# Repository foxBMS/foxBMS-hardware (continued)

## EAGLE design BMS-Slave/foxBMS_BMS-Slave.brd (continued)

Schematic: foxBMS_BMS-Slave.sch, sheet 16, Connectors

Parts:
X1601, X1602: 43045-0406_MOLEX_4PIN; X_SMD_MOLEX_43045-0408_R_REV01
X1603: 43045-1606_MOLEX_16PIN; X_SMD_MOLEX_43045-1608_R_REV01
X1604, X1607, X1608: MA10-2
X1605: MA09-2
X1606: 43045-2406_MOLEX_24PIN; X_SMD_MOLEX_43045-2408_R_REV01

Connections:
+3.0V_VREF2_0: X1604.18; also elsewhere on the board
+3.0V_VREF2_1: X1604.17; also elsewhere on the board
+5.0V_VREG_0: X1604.16; also elsewhere on the board
+5.0V_VREG_1: X1604.15; also elsewhere on the board
CELL_0+: X1603.2; also elsewhere on the board
CELL_0-: X1603.9; also elsewhere on the board
CELL_1+: X1603.10; also elsewhere on the board
CELL_2+: X1603.3; also elsewhere on the board
CELL_3+: X1603.11; also elsewhere on the board
CELL_4+: X1603.4; also elsewhere on the board
CELL_5+: X1603.12; also elsewhere on the board
CELL_6+: X1603.5; also elsewhere on the board
CELL_7+: X1603.13; also elsewhere on the board
CELL_8+: X1603.6; also elsewhere on the board
CELL_9+: X1603.14; also elsewhere on the board
CELL_10+: X1603.7; also elsewhere on the board
CELL_11+: X1603.15; also elsewhere on the board
FUSED_VBAT-: X1605.17, X1605.18, X1606.1, X1606.2, X1606.3, X1606.4, X1606.5, X1606.6, X1606.7, X1606.8, X1606.9, X1606.10, X1606.11, X1606.12, X1607.2, X1607.4, X1607.6, X1607.8, X1607.10, X1607.12, X1607.14, X1607.16, X1607.18, X1607.20, X1608.2, X1608.4, X1608.6, X1608.8, X1608.10, X1608.12, X1608.14, X1608.16, X1608.18, X1608.20; also elsewhere on the board
PRIMARY-GPIO0-OPT: X1604.6; also elsewhere on the board
PRIMARY-GPIO1: X1604.8; also elsewhere on the board
PRIMARY-GPIO2: X1604.10; also elsewhere on the board
PRIMARY-GPIO3-OPT: X1604.12; also elsewhere on the board
PRIMARY-GPIO4-OPT: X1604.14; also elsewhere on the board
PRIMARY-IN+_P: X1601.1; also elsewhere on the board
PRIMARY-IN-_N: X1601.3; also elsewhere on the board
PRIMARY-OUT+_P: X1601.4; also elsewhere on the board
PRIMARY-OUT-_N: X1601.2; also elsewhere on the board
PRIMARY-WDT: X1604.20; also elsewhere on the board
PRIMARY_D/A_INPUT_0: X1605.1; also elsewhere on the board
PRIMARY_D/A_INPUT_1: X1605.2; also elsewhere on the board
PRIMARY_D/A_INPUT_2: X1605.3; also elsewhere on the board
PRIMARY_D/A_INPUT_3: X1605.4; also elsewhere on the board
PRIMARY_D/A_INPUT_4: X1605.5; also elsewhere on the board
PRIMARY_D/A_INPUT_5: X1605.6; also elsewhere on the board
PRIMARY_D/A_INPUT_6: X1605.7; also elsewhere on the board
PRIMARY_D/A_INPUT_7: X1605.8; also elsewhere on the board
PRIMARY_D/A_INPUT_8: X1605.9; also elsewhere on the board
PRIMARY_D/A_INPUT_9: X1605.10; also elsewhere on the board
PRIMARY_D/A_INPUT_10: X1605.11; also elsewhere on the board
PRIMARY_D/A_INPUT_11: X1605.12; also elsewhere on the board
PRIMARY_D/A_INPUT_12: X1605.13; also elsewhere on the board
PRIMARY_D/A_INPUT_13: X1605.14; also elsewhere on the board
PRIMARY_D/A_INPUT_14: X1605.15; also elsewhere on the board
PRIMARY_D/A_INPUT_15: X1605.16; also elsewhere on the board
SECONDARY-GPIO0-OPT: X1604.5; also elsewhere on the board
SECONDARY-GPIO1: X1604.7; also elsewhere on the board
SECONDARY-GPIO2: X1604.9; also elsewhere on the board
SECONDARY-GPIO3-OPT: X1604.11; also elsewhere on the board
SECONDARY-GPIO4-OPT: X1604.13; also elsewhere on the board
SECONDARY-IN+_P: X1602.1; also elsewhere on the board
SECONDARY-IN-_N: X1602.3; also elsewhere on the board
SECONDARY-OUT+_P: X1602.4; also elsewhere on the board
SECONDARY-OUT-_N: X1602.2; also elsewhere on the board
SECONDARY-WDT: X1604.19; also elsewhere on the board
SECONDARY_D/A_INPUT_0: X1604.1; also elsewhere on the board
SECONDARY_D/A_INPUT_1: X1604.2; also elsewhere on the board
SECONDARY_D/A_INPUT_2: X1604.3; also elsewhere on the board
SECONDARY_D/A_INPUT_3: X1604.4; also elsewhere on the board
T-SENSOR_0: X1606.24; also elsewhere on the board
T-SENSOR_1: X1606.23; also elsewhere on the board
T-SENSOR_2: X1606.22; also elsewhere on the board
T-SENSOR_3: X1606.21; also elsewhere on the board
T-SENSOR_4: X1606.20; also elsewhere on the board
T-SENSOR_5: X1606.19; also elsewhere on the board
T-SENSOR_6: X1607.1; also elsewhere on the board
T-SENSOR_7: X1607.3; also elsewhere on the board
T-SENSOR_8: X1607.5; also elsewhere on the board
T-SENSOR_9: X1607.7; also elsewhere on the board
T-SENSOR_10: X1607.9; also elsewhere on the board
T-SENSOR_11: X1607.11; also elsewhere on the board
T-SENSOR_12: X1607.13; also elsewhere on the board
T-SENSOR_13: X1607.15; also elsewhere on the board
T-SENSOR_14: X1607.17; also elsewhere on the board
T-SENSOR_15: X1607.19; also elsewhere on the board
T-SENSOR_16: X1606.18; also elsewhere on the board
T-SENSOR_17: X1606.17; also elsewhere on the board
T-SENSOR_18: X1606.16; also elsewhere on the board
T-SENSOR_19: X1606.15; also elsewhere on the board
T-SENSOR_20: X1606.14; also elsewhere on the board
T-SENSOR_21: X1606.13; also elsewhere on the board
T-SENSOR_22: X1608.19; also elsewhere on the board
T-SENSOR_23: X1608.17; also elsewhere on the board
T-SENSOR_24: X1608.15; also elsewhere on the board
T-SENSOR_25: X1608.13; also elsewhere on the board
T-SENSOR_26: X1608.11; also elsewhere on the board
T-SENSOR_27: X1608.9; also elsewhere on the board
T-SENSOR_28: X1608.7; also elsewhere on the board
T-SENSOR_29: X1608.5; also elsewhere on the board
T-SENSOR_30: X1608.3; also elsewhere on the board
T-SENSOR_31: X1608.1; also elsewhere on the board
VBAT+: X1603.16; also elsewhere on the board
VBAT-: X1603.1; also elsewhere on the board

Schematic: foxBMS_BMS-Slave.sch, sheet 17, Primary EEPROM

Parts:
C1701: 100nF, 20%, 16V; 0603
IC1701: 24AA02UID; IC_SMD_SOT23-5_R_MICROCHIP_REV01

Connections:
+5.0V_VREG_0: C1701.2, IC1701.4 (VCC); also elsewhere on the board
FUSED_VBAT-: C1701.1, IC1701.2 (VSS); also elsewhere on the board
PRIMARY-SCL: IC1701.1 (SCL); also elsewhere on the board
PRIMARY-SDA: IC1701.3 (SDA); also elsewhere on the board

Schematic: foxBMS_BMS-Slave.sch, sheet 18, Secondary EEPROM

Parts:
C1801: 100nF, 20%, 16V; 0603
IC1801: 24AA02UID; IC_SMD_SOT23-5_R_MICROCHIP_REV01

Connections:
+5.0V_VREG_1: C1801.2, IC1801.4 (VCC); also elsewhere on the board
FUSED_VBAT-: C1801.1, IC1801.2 (VSS); also elsewhere on the board
SECONDARY-SCL: IC1801.1 (SCL); also elsewhere on the board
SECONDARY-SDA: IC1801.3 (SDA); also elsewhere on the board

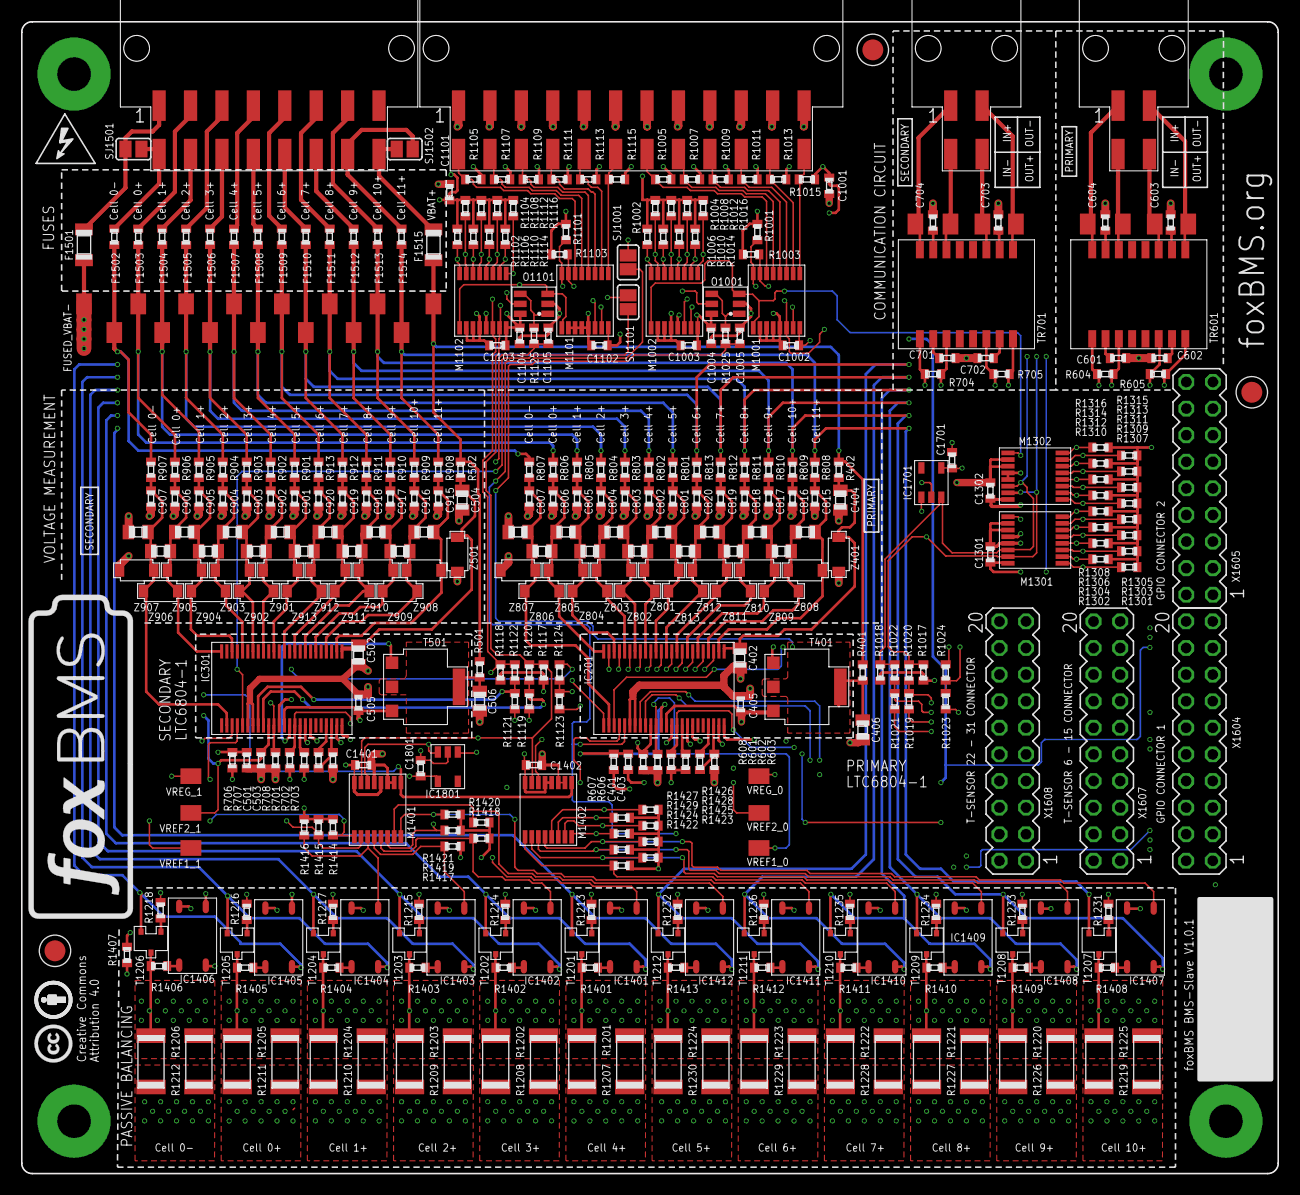
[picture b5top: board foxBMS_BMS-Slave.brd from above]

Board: 6 copper layers, 120.0 x 110.0 mm, 394 parts (0 on the bottom side), 244 nets.

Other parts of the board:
U$50, U$52, U$62: FIDUCIAL_1MM

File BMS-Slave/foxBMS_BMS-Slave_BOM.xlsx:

Populate | Qty | Value | Device | Package | Parts | Comments | Farnell | Digikey | Mouser
Resistor
yes | 10 | 0R | R_0603 | 603 | R601 R607 R701 R707 R1020 R1022 R1024 R1120 R1122 R1124 | Resistor | 2059527
yes | 2 | 1.21k, 1%, 1/10W | R_0603 | 603 | R603 R703 | Resistor | 2059331
yes | 32 | 100R, 1%, 1/10W | R_0603 | 603 | R401 R402 R501 R502 R801 R802 R803 R804 R805 R806 R807 R808 R809 R810 R811 R812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 | Resistor | 2059574
yes | 32 | 10k, 10%, 1/10W | R_0603 | 603 | R1301 R1302 R1303 R1304 R1305 R1306 R1307 R1308 R1309 R1310 R1311 R1312 R1313 R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 | Resistor | 2303192
yes | 24 | 75R, 10%, 0.4W | R2010 | 2010 | R1201 R1202 R1203 R1204 R1205 R1206 R1207 R1208 R1209 R1210 R1211 R1212 R1219 R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 | Resistor | 2059282
yes | 4 | 120R, 1%, 1/10W | R_0603 | 603 | R604 R605 R704 R705 | Resistor | 2303067
yes | 2 | 1M, 10%, 1/10W | R_0603 | 603 | R608 R708 | Resistor | 2059679
yes | 1 | 1k, 10%, 1/10W | R_0603 | 603 | R1407 | Resistor | 2059601
yes | 12 | 130R, 10%, 1/10W | R_0603 | 603 | R1401 R1402 R1403 R1404 R1405 R1406 R1408 R1409 R1410 R1411 R1412 R1413 | Resistor | 2059288
yes | 32 | 20k, 1%, 1/10W | R_0603 | 603 | R1001 R1002 R1003 R1004 R1005 R1006 R1007 R1008 R1009 R1010 R1011 R1012 R1013 R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 | Resistor | 2059636
yes | 12 | 3.3k, 10%, 1/10W | R_0603 | 603 | R1213 R1214 R1215 R1216 R1217 R1218 R1231 R1232 R1233 R1234 R1235 R1236 | Resistor | 2059614
yes | 4 | 4.7k, 10%, 1/10W | R_0603 | 603 | R1017 R1018 R1117 R1118 | Resistor | 2059619
yes | 2 | 806, 1%, 1/10W | R_0603 | 603 | R602 R702 | Resistor | 2059324 | 541-806HCT-ND
Capacitor
yes | 6 | 100nF, 10%, 100V | C_0805 | 805 | C402 C404 C406 C502 C504 C506 | Capacitor | 1856515
yes | 4 | 100nF, 20%, 16V | C_0603 | 603 | C1001 C1101 C1701 C1801 | Capacitor | 1828890
yes | 4 | 100pF, 15%, 25V | C_0603 | 603 | C601 C602 C701 C702 | Capacitor | 1856386
yes | 28 | 10nF, 100V, 10% | C_0603 | 603 | C801 C802 C803 C804 C805 C806 C807 C815 C816 C817 C818 C819 C820 C901 C902 C903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 | Capacitor | 1865545
yes | 16 | 1uF, 20%, 16V | C_0603 | 603 | C401 C403 C405 C501 C503 C505 C1002 C1003 C1004 C1102 C1103 C1104 C1301 C1302 C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 | Capacitor | 1907343
yes | 4 | 1uF, 20%, 25V | C_0603 | 603 | C603 C604 C703 C704 | Capacitor | 2470425
Diode
yes | 26 | 6.8V, 500mW | MMSZ5235BT1G | SOD123 | Z801 Z802 Z803 Z804 Z805 Z806 Z807 Z808 Z809 Z810 Z811 Z812 Z813 Z901 Z902 Z903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 | ON SEMICONDUCTOR | 1431277
yes | 2 | 60V,500mW | MMSZ5264B-V-GS08 | SOD123 | Z401 Z501 | MMSZ_xVx_T1 Seri | 1895056
yes | 12 | CPC1008N | CPC1008N | SOP4 | IC1401 IC1402 IC1403 IC1404 IC1405 IC1406 IC1407 IC1408 IC1409 IC1410 IC1411 IC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 | CLARE - Single-Po | 1653755
IC
yes | 8 | LTC1380-GN | LTC1380-GN | SSOP16 | M1001 M1002 M1101 M1102 M1301 M1302 M1401 M1402 |  | 2295514
yes | 2 | LTC6255CS6PBF | LTC6255CS6PBF | SOT95P280X100-6N | O1001 O1101 | Op Amps |  | LTC6255CS6#TRMPBFCT-ND
yes | 2 | LTC6804-1 | LTC6804-1 | SSOP48 | IC201 IC301 |  |  | LTC6804HG-1#PBF-ND
yes | 2 | 24AA02UID | SOT-23 | SOT-23 | IC1701 IC1801 | EEPROM IC | 2345557 | 24AA02UIDT-I/OTCT-ND | 579-24AA02UIDT-I/OT
Connector
yes | 1 | MA09-2 | MA09-2 | MA09-2 | X1605 | PIN HEADER | 2025256
yes | 3 | MA10-2 | MA10-2 | MA10-2 | X1604 X1607 X1608 | PIN HEADER | 2025257
yes | 1 |  | HEADER_POS16_43045-1606 | 43045-1606 | X1603 | Molex - Micro-Fit |  | WM10739CT-ND
yes | 1 |  | HEADER_POS24_43045-2406 | 43045-2406 | X1606 | Molex - Micro-Fit |  | WM10768CT-ND
yes | 2 |  | HEADER_POS4_43045-0406 | 43045-0406 | X1601 X1602 | Molex - Micro-Fit | 2063766 | WM3249CT-ND
Transistor
yes | 12 | NX2301P | NX2301P | SOT23 | T1201 T1202 T1203 T1204 T1205 T1206 T1207 T1208 T1209 T1210 T1211 T1212 | #2245 | 1894738
yes | 2 | PBHV8115Z | NPN-223 | SOT-223 | T401 T501 |  | 1829309
Misc
yes | 2 | 0.5A, 63V, 0.25R | R_MET_1206 | 1206 | F1501 F1515 | Resistor |  | F1454CT-ND
yes | 2 | HX1188NL | HX1188NL | HX1188NL | T601 T701 |  |  | 553-1536-1-ND
yes | 13 | FUSE: 0.250A, 32V, 0.57R | R_0603 | 603 | F1502 F1503 F1504 F1505 F1506 F1507 F1508 F1509 F1510 F1511 F1512 F1513 F1514 | Resistor |  | F1389CT-ND
no | 26 | OPT: 100nF, 25V | C_0805 | 805 | C808 C809 C810 C811 C812 C813 C814 C821 C822 C823 C824 C825 C826 C908 C909 C910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 | Capacitor
no | 29 | PAD_2.0X1.5MM | PAD_2.0X1.5MM | PAD2.0X1.5MM | LSP401 LSP402 LSP403 LSP501 LSP502 LSP503 LSP601 LSP602 LSP603 LSP604 LSP701 LS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 | Testpoint

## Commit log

2017-02-07 Added hardware files.
2017-02-13 Added license file (same license as already found in the documentation).
2017-03-16 In BMS-Master layout and schematic, fixed Murata NCS6 DC/DC converter library (design rule violation).
2017-03-17 Modify formatting in README.md
2017-05-08 Correction of the link to HTTPS (Lorentz)
2017-05-09 Minor corrections (Lorentz)
2017-05-10 Minor updates and corrections of notations, wording and bill of materials (V1.0.1). No changes in schematic and layout.
2017-05-11 Corrected BOM.
2017-05-12 Fixed silkscreen for IC803 on BMS-Extension
2017-06-07 Updated LICENSE.md
2017-06-09 Changed ADUM1xxx to ADUM3xxx in schematic of BMS-Master and BMS-Extension
2017-09-04 updated foxBMS-slave to version 2.02
2017-10-24 - update README.md - removed trailing whitespace
2017-11-02 updated foxBMS-slave to version 2.1.0
